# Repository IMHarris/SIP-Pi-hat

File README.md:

# SIP Pi HAT

Raspberry Pi HAT for the [SIP (Smart Irrigation Program)](https://github.com/Dan-in-CA/SIP) irrigation controller.

## Features

- Designed to interface with SIP irrigation controller on Raspberry Pi
- Outputs for relay control of up to 16 stations with 74HC595 output header for more
- XAIO ESP32C3 module for flow sensor monitoring with inputs for hall flow sensor. Designed to work with the flow plugin
- Communicates flow sensor data to Pi via UART
- 5v I2c headers. Great for LCD plugin.

## Hardware

This project contains KiCad 7+ design files:
- `SIP_Hat.kicad_sch` - Schematic
- `SIP_Hat.kicad_pcb` - PCB layout
- `SIP_Hat.kicad_pro` - Project file
- `Gerber/` - Manufacturing files

## Firmware

The ESP32C3 firmware is available in the companion repository: [flow-sensor-esp32](https://github.com/IMHarris/flow-sensor-esp32)

## Bill of Materials

See `SIP_Hat.csv` for the complete BOM.

## Related Projects

- [SIP Irrigation Controller](https://github.com/Dan-in-CA/SIP)
- [SIP Plugins](https://github.com/Dan-in-CA/sip_plugins)
- [ESP32C3 Flow Sensor Firmware](https://github.com/IMHarris/flow-sensor-esp32)

## License

This hardware design is licensed under [CC BY-SA 4.0](http://creativecommons.org/licenses/by-sa/4.0/).

You are free to share and adapt this work, provided you give appropriate credit and distribute your contributions under the same license.

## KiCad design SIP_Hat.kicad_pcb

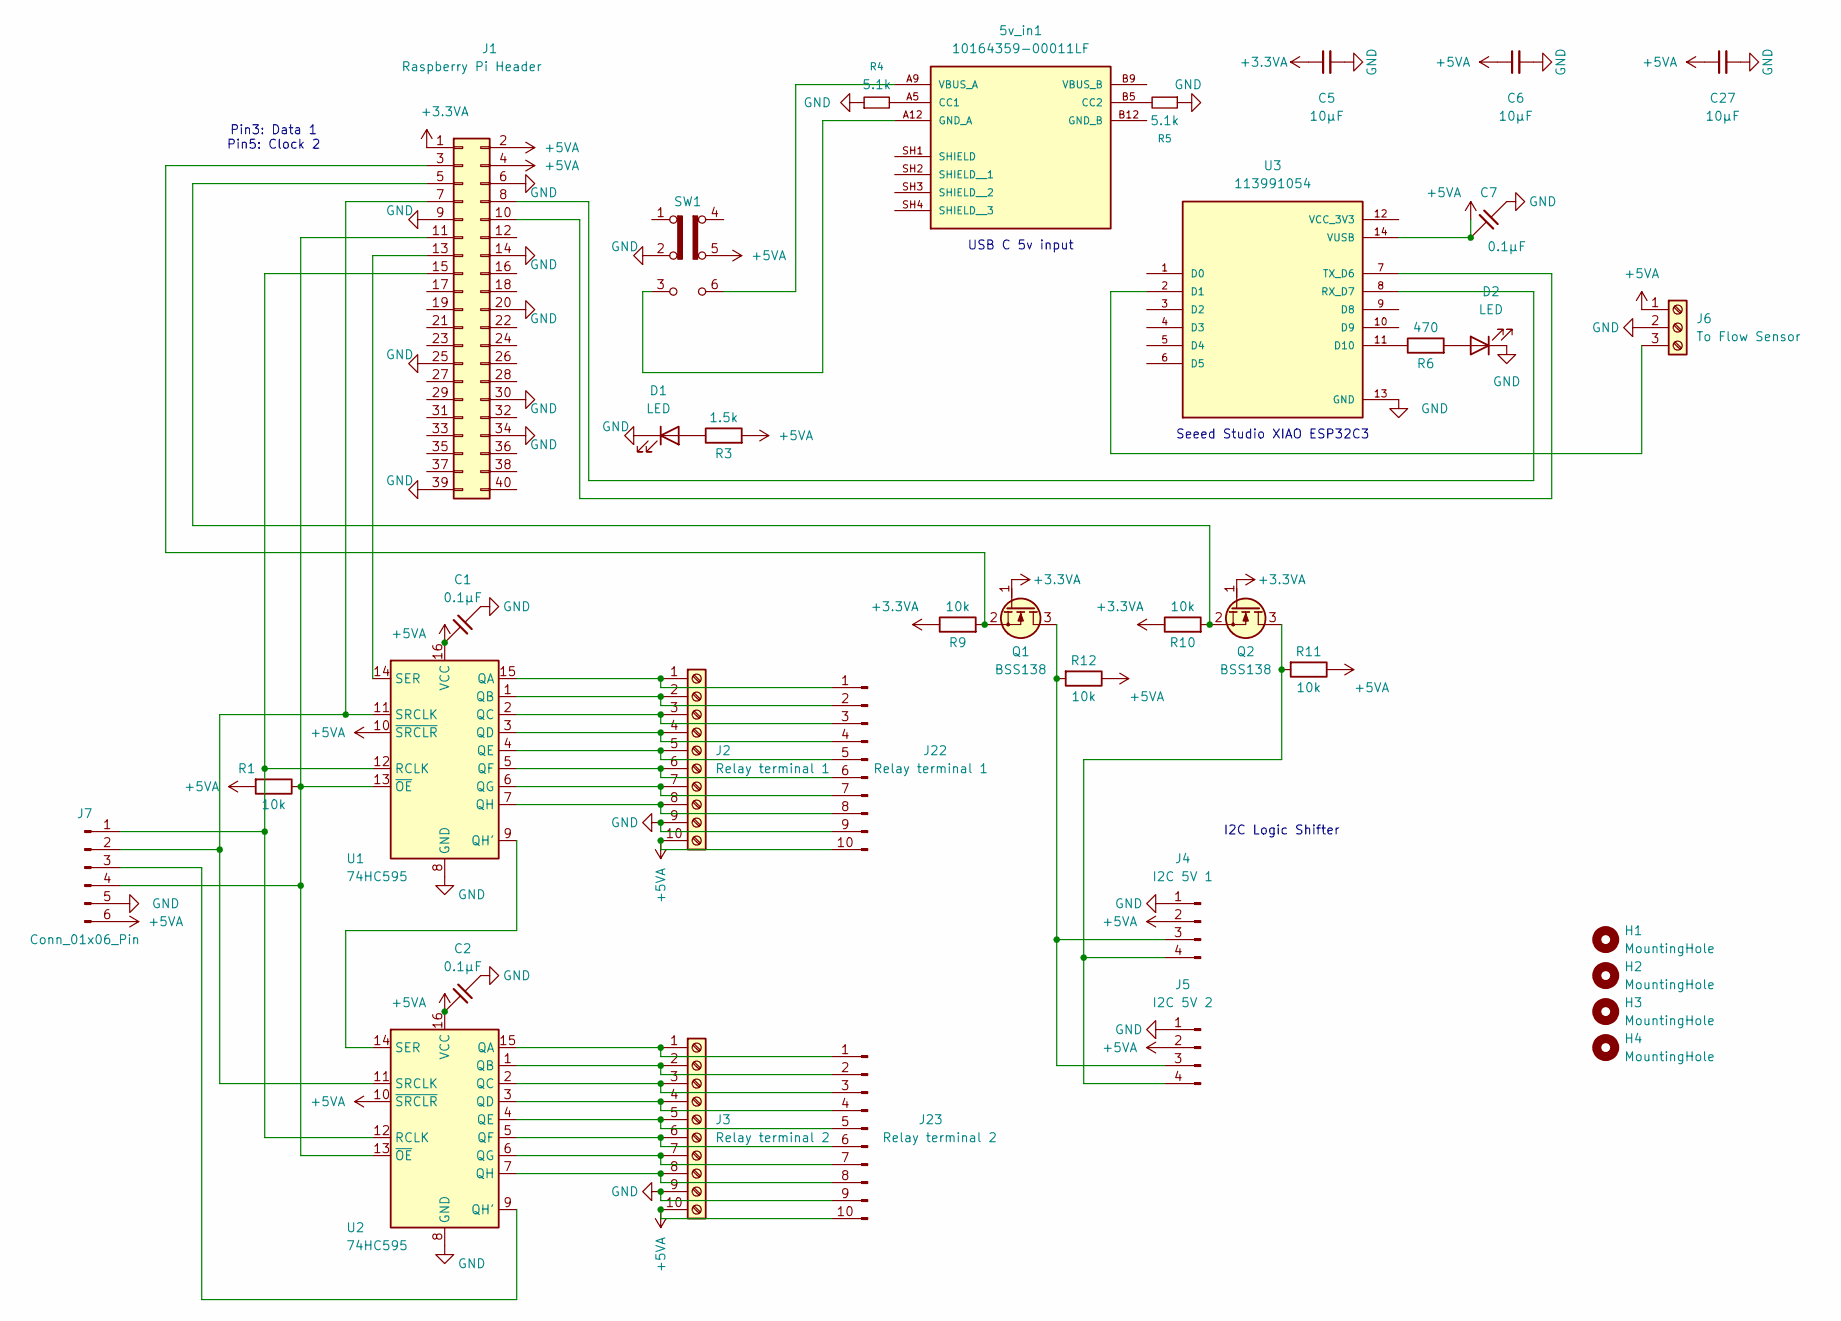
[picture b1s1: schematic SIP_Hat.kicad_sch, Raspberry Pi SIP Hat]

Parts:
5v_in1: 10164359-00011LF; AMPHENOL_10164359-00011LF; PARTREV A
C1, C2, C7: 0.1µF; C_0805_2012Metric_Pad1.18x1.45mm_HandSolder
C5, C6, C27: 10µF; C_1206_3216Metric_Pad1.33x1.80mm_HandSolder
D1, D2: LED; LED_1206_3216Metric_Pad1.42x1.75mm
H1, H2, H3, H4: MountingHole; MountingHole_2.7mm_M2.5_ISO14580
J1: Raspberry Pi Header; PinHeader_2x20_P2.54mm_Vertical
J2: Relay terminal 1; PHOENIX_1990083
J3: Relay terminal 2; PHOENIX_1990083
J4: I2C 5V 1; PinHeader_1x04_P2.54mm_Vertical
J5: I2C 5V 2; PinHeader_1x04_P2.54mm_Vertical
J6: To Flow Sensor; PHOENIX_1729131
J7: Conn_01x06_Pin; PinHeader_1x06_P2.54mm_Vertical
J22: Relay terminal 1; Molex_SL_171971-0010_1x10_P2.54mm_Vertical
J23: Relay terminal 2; Molex_SL_171971-0010_1x10_P2.54mm_Vertical
Q1, Q2: BSS138; SOT-23
R1, R9, R10, R11, R12: 10k; R_1206_3216Metric_Pad1.30x1.75mm_HandSolder
R3: 1.5k; R_1206_3216Metric_Pad1.30x1.75mm_HandSolder
R4, R5: 5.1k; R_1206_3216Metric_Pad1.30x1.75mm_HandSolder
R6: 470; R_1206_3216Metric_Pad1.30x1.75mm_HandSolder
SW1: SW_Slide_DPDT; DPDT Slide switch - CL-SB-22C-02
U1, U2: 74HC595; DIP-16_W7.62mm_Socket
U3: 113991054; MODULE_113991054; PARTREV 23/05/2022

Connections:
+3.3VA: C5.1, J1.1, Q1.1 (G), Q2.1 (G), R9.1, R10.1
+5VA: C1.2, C2.2, C6.1, C7.2, C27.1, J1.2, J1.4, J2.10, J3.10, J4.2, J5.2, J6.1, J7.6, J22.10, J23.10, R1.2, R3.2, R11.1, R12.1, SW1.5 (B), U1.10 (~SRCLR), U1.16 (VCC), U2.10 (~SRCLR), U2.16 (VCC), U3.14 (VUSB)
GND: C1.1, C2.1, C5.2, C6.2, C7.1, C27.2, D1.1 (K), D2.1 (K), J1.6, J1.9, J1.14, J1.20, J1.25, J1.30, J1.34, J1.39, J2.9, J3.9, J4.1, J5.1, J6.2, J7.5, J22.9, J23.9, R4.1, R5.1, SW1.2 (B), U1.8 (GND), U2.8 (GND), U3.13 (GND)
unnamed: 5v_in1.A5 (CC1), R4.2
unnamed: 5v_in1.B5 (CC2), R5.2
unnamed: 5v_in1.A12 (GND_A), SW1.3 (C)
unnamed: 5v_in1.A9 (VBUS_A), SW1.6 (A)
unnamed: D1.2 (A), R3.1
unnamed: D2.2 (A), R6.2
unnamed: J1.3, Q1.2 (S), R9.2
unnamed: J1.5, Q2.2 (S), R10.2
unnamed: J1.7, J7.2, U1.11 (SRCLK), U2.11 (SRCLK)
unnamed: J1.8, U3.8 (RX_D7)
unnamed: J1.10, U3.7 (TX_D6)
unnamed: J1.11, J7.4, R1.1, U1.13 (~OE), U2.13 (~OE)
unnamed: J1.13, U1.14 (SER)
unnamed: J1.15, J7.1, U1.12 (RCLK), U2.12 (RCLK)
unnamed: J2.1, J22.1, U1.15 (QA)
unnamed: J2.2, J22.2, U1.1 (QB)
unnamed: J2.3, J22.3, U1.2 (QC)
unnamed: J2.4, J22.4, U1.3 (QD)
unnamed: J2.5, J22.5, U1.4 (QE)
unnamed: J2.6, J22.6, U1.5 (QF)
unnamed: J2.7, J22.7, U1.6 (QG)
unnamed: J2.8, J22.8, U1.7 (QH)
unnamed: J4.3, J5.3, Q1.3 (D), R12.2
unnamed: J4.4, J5.4, Q2.3 (D), R11.2
unnamed: J6.3, U3.2 (D1)
unnamed: J7.3, U2.9 (QH')
unnamed: J3.1, J23.1, U2.15 (QA)
unnamed: J3.2, J23.2, U2.1 (QB)
unnamed: J3.3, J23.3, U2.2 (QC)
unnamed: J3.4, J23.4, U2.3 (QD)
unnamed: J3.5, J23.5, U2.4 (QE)
unnamed: J3.6, J23.6, U2.5 (QF)
unnamed: J3.7, J23.7, U2.6 (QG)
unnamed: J3.8, J23.8, U2.7 (QH)
unnamed: U1.9 (QH'), U2.14 (SER)
unnamed: R6.1, U3.11 (D10)

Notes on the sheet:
USB C 5v input
I2C Logic Shifter
Seeed Studio XIAO ESP32C3
Pin3: Data 1 Pin5: Clock 2

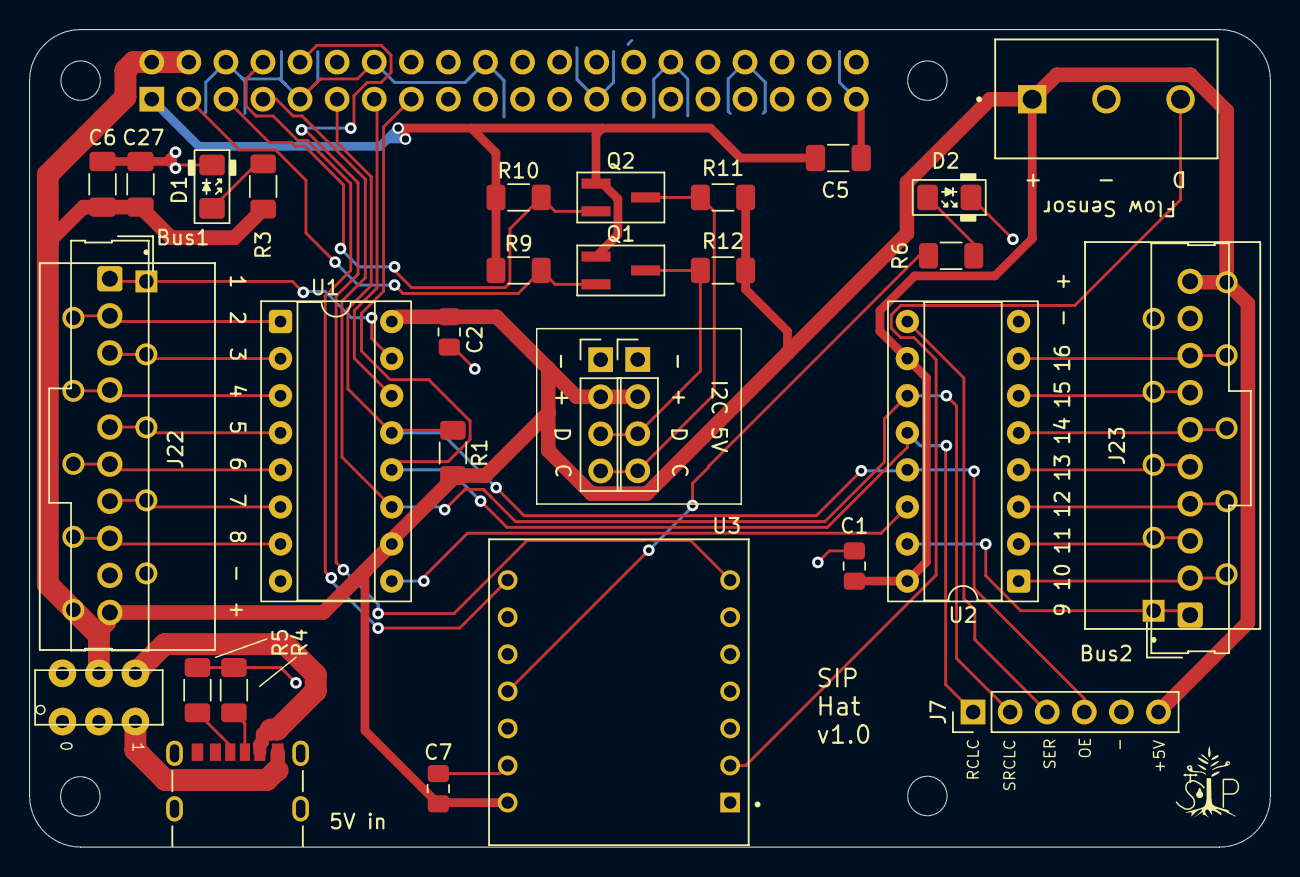
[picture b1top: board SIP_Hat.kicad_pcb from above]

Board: 2 copper layers, 85.0 x 56.0 mm, 37 parts (0 on the bottom side), 39 nets.

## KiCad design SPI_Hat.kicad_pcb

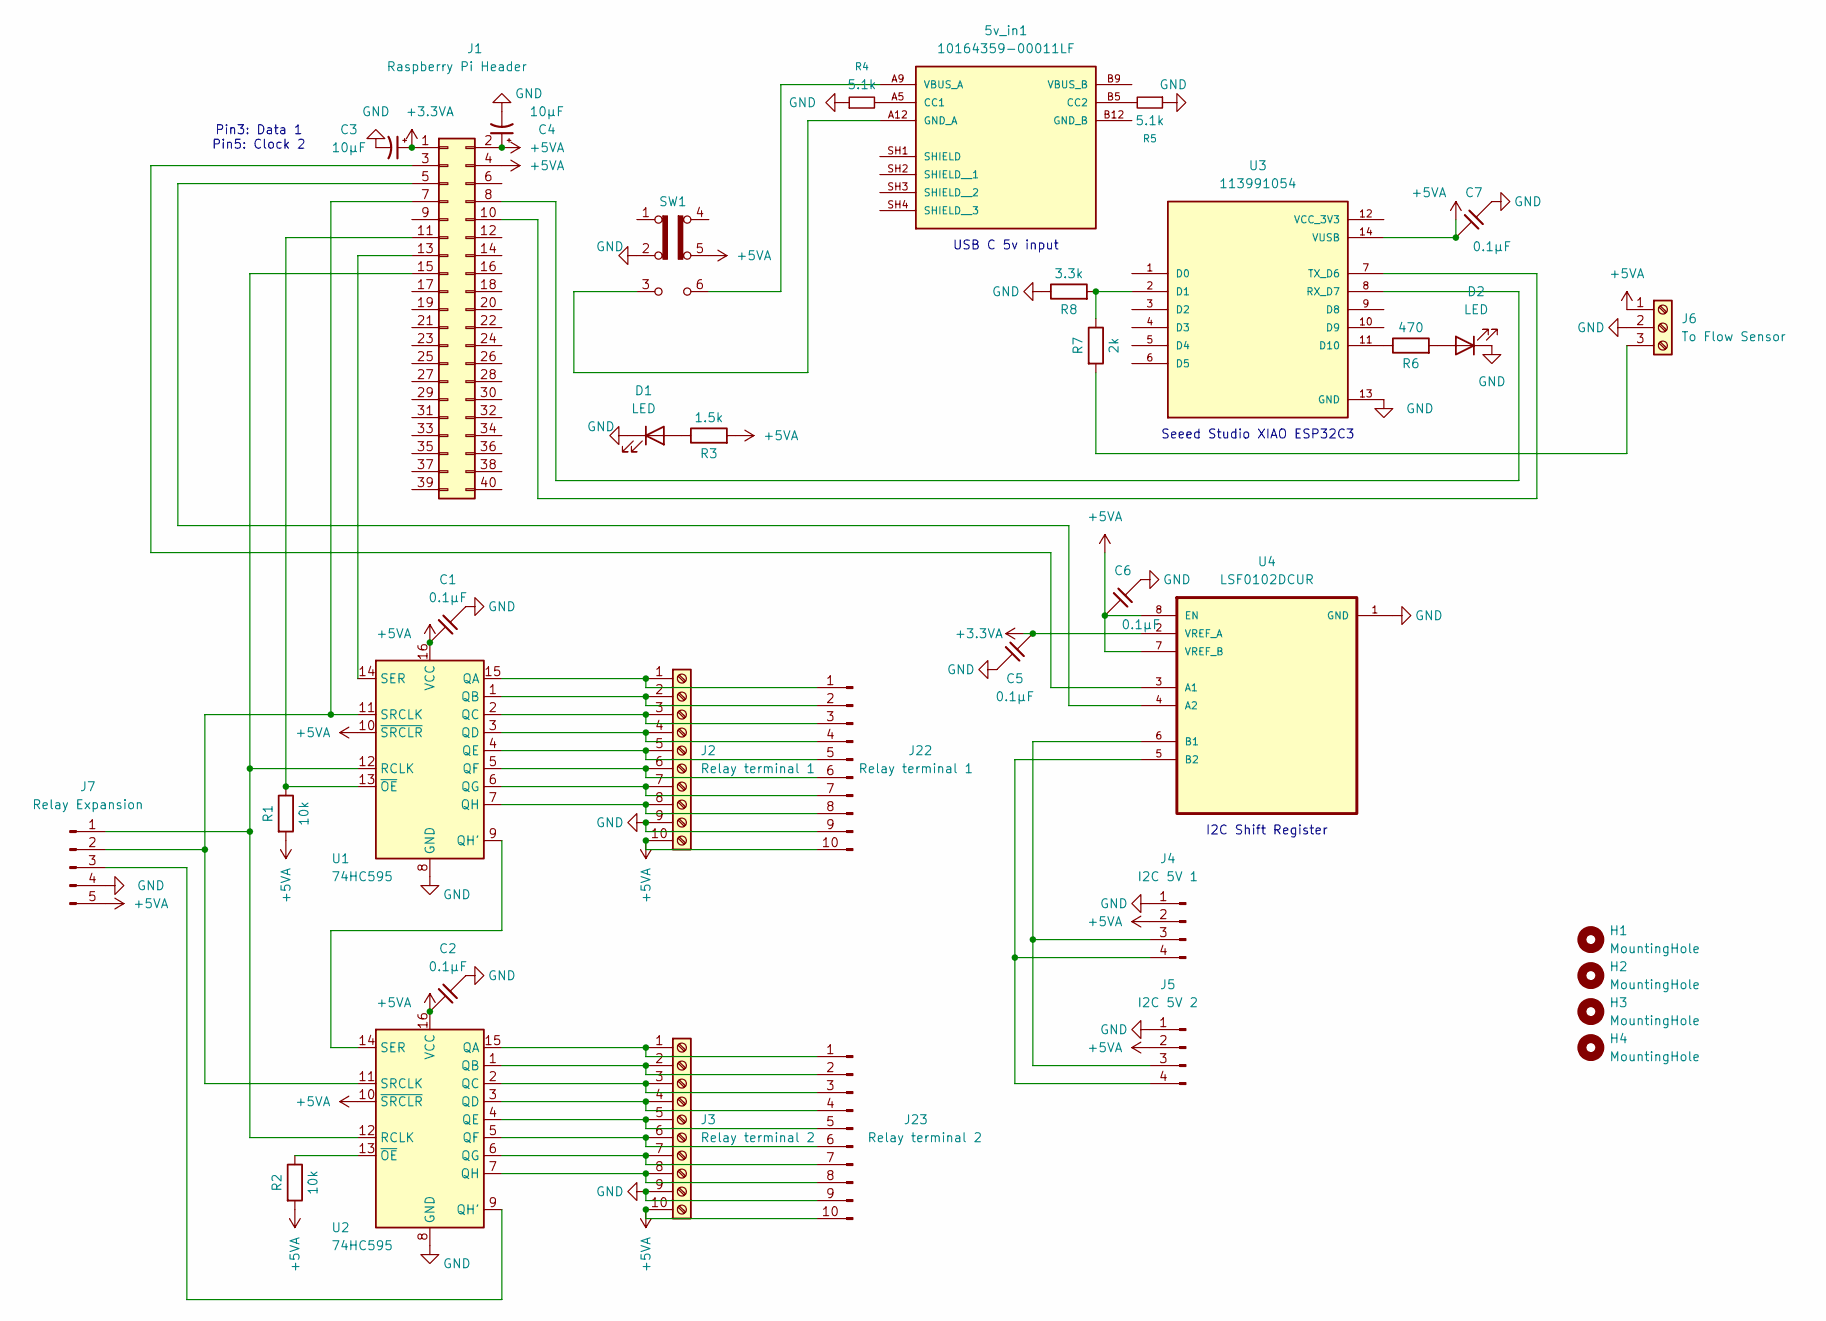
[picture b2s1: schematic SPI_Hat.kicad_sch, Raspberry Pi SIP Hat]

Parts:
5v_in1: 10164359-00011LF; AMPHENOL_10164359-00011LF; PARTREV A
C1, C2, C5, C6, C7: 0.1µF; C_0805_2012Metric_Pad1.18x1.45mm_HandSolder
C3, C4: 10µF; CP_Radial_D5.0mm_P2.50mm
D1, D2: LED; LED_1206_3216Metric_Pad1.42x1.75mm
H1, H2, H3, H4: MountingHole; MountingHole_2.7mm_M2.5_ISO14580
J1: Raspberry Pi Header; PinHeader_2x20_P2.54mm_Vertical
J2: Relay terminal 1; PHOENIX_1990083
J3: Relay terminal 2; PHOENIX_1990083
J4: I2C 5V 1; PinHeader_1x04_P2.54mm_Vertical
J5: I2C 5V 2; PinHeader_1x04_P2.54mm_Vertical
J6: To Flow Sensor; PHOENIX_1729131
J7: Relay Expansion; PinHeader_1x05_P2.54mm_Vertical
J22: Relay terminal 1; Molex_SL_171971-0010_1x10_P2.54mm_Vertical
J23: Relay terminal 2; Molex_SL_171971-0010_1x10_P2.54mm_Vertical
R1, R2: 10k; R_1206_3216Metric_Pad1.30x1.75mm_HandSolder
R3: 1.5k; R_1206_3216Metric_Pad1.30x1.75mm_HandSolder
R4, R5: 5.1k; R_1206_3216Metric_Pad1.30x1.75mm_HandSolder
R6: 470; R_1206_3216Metric_Pad1.30x1.75mm_HandSolder
R7: 2k; R_1206_3216Metric_Pad1.30x1.75mm_HandSolder
R8: 3.3k; R_1206_3216Metric_Pad1.30x1.75mm_HandSolder
SW1: SW_Slide_DPDT; DPDT Slide switch - CL-SB-22C-02
U1, U2: 74HC595; DIP-16_W7.62mm_Socket
U3: 113991054; MODULE_113991054; PARTREV 23/05/2022
U4: LSF0102DCUR; SOP50P310X90-8N

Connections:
+3.3VA: C3.1, C5.2, J1.1, U4.2 (VREF_A)
+5VA: C1.2, C2.2, C4.1, C6.2, C7.2, J1.2, J1.4, J2.10, J3.10, J4.2, J5.2, J6.1, J7.5, J22.10, J23.10, R1.2, R2.2, R3.2, SW1.5 (B), U1.10 (~SRCLR), U1.16 (VCC), U2.10 (~SRCLR), U2.16 (VCC), U3.14 (VUSB), U4.7 (VREF_B), U4.8 (EN); also elsewhere on the board
GND: C1.1, C2.1, C3.2, C4.2, C5.1, C6.1, C7.1, D1.1 (K), D2.1 (K), J2.9, J3.9, J4.1, J5.1, J6.2, J7.4, J22.9, J23.9, R4.1, R5.1, R8.1, SW1.2 (B), U1.8 (GND), U2.8 (GND), U3.13 (GND), U4.1 (GND); also elsewhere on the board
unnamed: 5v_in1.A5 (CC1), R4.2
unnamed: 5v_in1.B5 (CC2), R5.2
unnamed: 5v_in1.A12 (GND_A), SW1.3 (C)
unnamed: 5v_in1.A9 (VBUS_A), SW1.6 (A)
unnamed: D1.2 (A), R3.1
unnamed: D2.2 (A), R6.2
unnamed: J1.3 (GPIO2), U4.3 (A1)
unnamed: J1.5 (GPIO3), U4.4 (A2)
unnamed: J1.7, J7.2, U1.11 (SRCLK), U2.11 (SRCLK)
unnamed: J1.8, U3.8 (RX_D7)
unnamed: J1.10, U3.7 (TX_D6)
unnamed: J1.11, R1.1, U1.13 (~OE)
unnamed: J1.13, U1.14 (SER)
unnamed: J1.15, J7.1, U1.12 (RCLK), U2.12 (RCLK)
unnamed 17: J2.1, J22.1, U1.15 (QA); also elsewhere on the board
unnamed 18: J2.2, J22.2, U1.1 (QB); also elsewhere on the board
unnamed 19: J2.3, J22.3, U1.2 (QC); also elsewhere on the board
unnamed 20: J2.4, J22.4, U1.3 (QD); also elsewhere on the board
unnamed 21: J2.5, J22.5, U1.4 (QE); also elsewhere on the board
unnamed 22: J2.6, J22.6, U1.5 (QF); also elsewhere on the board
unnamed 23: J2.7, J22.7, U1.6 (QG); also elsewhere on the board
unnamed 24: J2.8, J22.8, U1.7 (QH); also elsewhere on the board
unnamed 25: J3.1, J23.1, U2.15 (QA); also elsewhere on the board
unnamed 26: J3.2, J23.2, U2.1 (QB); also elsewhere on the board
unnamed 27: J3.3, J23.3, U2.2 (QC); also elsewhere on the board
unnamed 28: J3.4, J23.4, U2.3 (QD); also elsewhere on the board
unnamed 29: J3.5, J23.5, U2.4 (QE); also elsewhere on the board
unnamed 30: J3.6, J23.6, U2.5 (QF); also elsewhere on the board
unnamed 31: J3.7, J23.7, U2.6 (QG); also elsewhere on the board
unnamed 32: J3.8, J23.8, U2.7 (QH); also elsewhere on the board
unnamed: J4.3, J5.3, U4.6 (B1)
unnamed: J4.4, J5.4, U4.5 (B2)
unnamed: J6.3, R7.2
unnamed: J7.3, U2.9 (QH')
unnamed: U1.9 (QH'), U2.14 (SER)
unnamed: R2.1, U2.13 (~OE)
unnamed: R7.1, R8.2, U3.2 (D1)
unnamed: R6.1, U3.11 (D10)

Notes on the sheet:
USB C 5v input
I2C Shift Register
Seeed Studio XIAO ESP32C3
Pin3: Data 1 Pin5: Clock 2

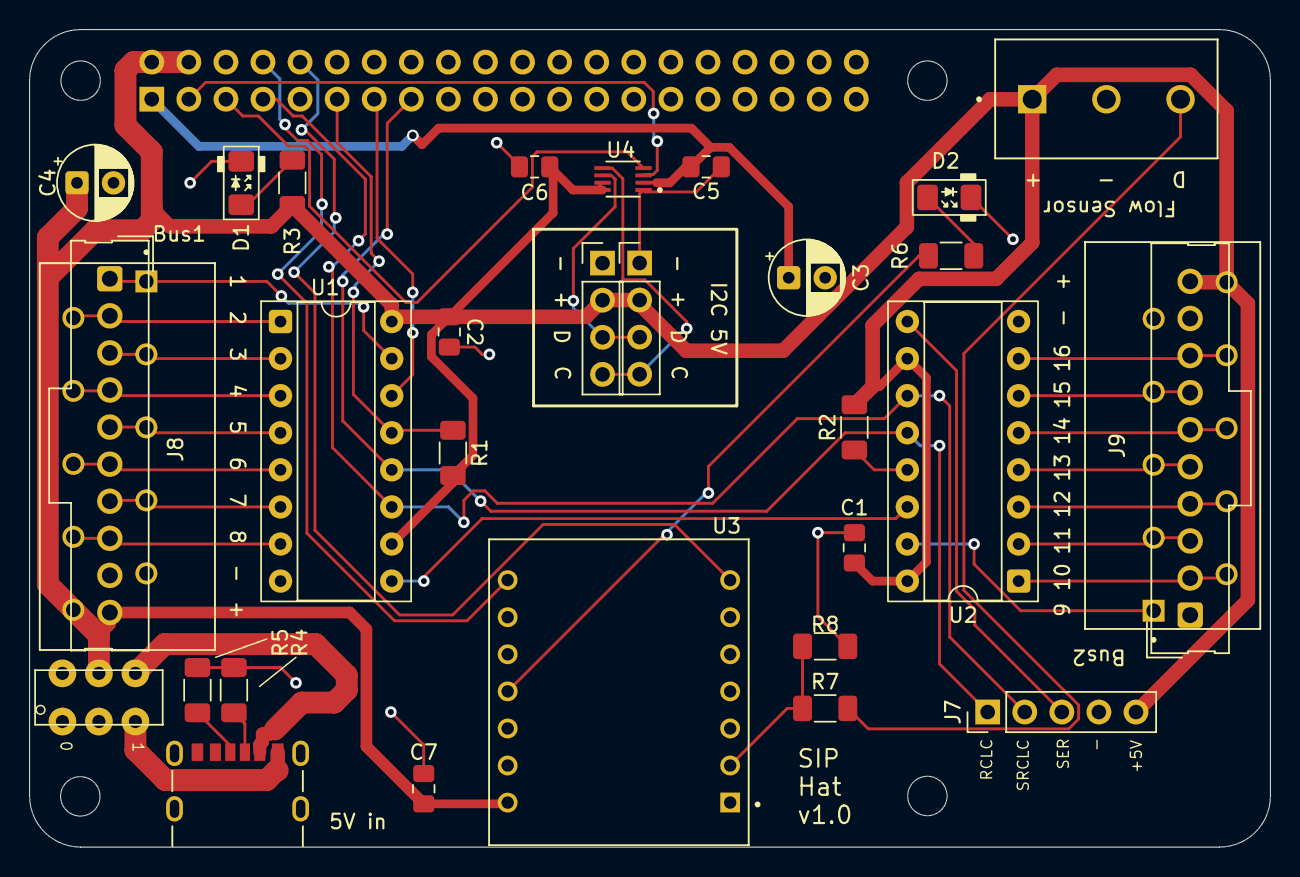
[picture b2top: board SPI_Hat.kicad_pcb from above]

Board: 2 copper layers, 85.0 x 56.0 mm, 36 parts (0 on the bottom side), 41 nets.

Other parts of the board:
J8, J9: Expansion; Molex_SL_171971-0010_1x10_P2.54mm_Vertical

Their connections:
+5VA: J8.10, J9.10; also elsewhere on the board
GND: J8.9, J9.9; also elsewhere on the board
unnamed 17: J8.1; also elsewhere on the board
unnamed 18: J8.2; also elsewhere on the board
unnamed 19: J8.3; also elsewhere on the board
unnamed 20: J8.4; also elsewhere on the board
unnamed 21: J8.5; also elsewhere on the board
unnamed 22: J8.6; also elsewhere on the board
unnamed 23: J8.7; also elsewhere on the board
unnamed 24: J8.8; also elsewhere on the board
unnamed 25: J9.1; also elsewhere on the board
unnamed 26: J9.2; also elsewhere on the board
unnamed 27: J9.3; also elsewhere on the board
unnamed 28: J9.4; also elsewhere on the board
unnamed 29: J9.5; also elsewhere on the board
unnamed 30: J9.6; also elsewhere on the board
unnamed 31: J9.7; also elsewhere on the board
unnamed 32: J9.8; also elsewhere on the board

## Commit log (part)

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2025-11-29 Update .gitignore to include Gerber files and exclude lock files
2025-11-29 Add Gerber manufacturing files for SIP Pi HAT
2025-12-03 Add CC BY-SA 4.0 license
2026-01-17 Rename project from SPI_Hat to SIP_Hat
    - Renamed all SPI_Hat files to SIP_Hat (correct project name)
    - Updated .gitignore to exclude additional KiCad autosave files
    - Added graphics assets and documentation image
